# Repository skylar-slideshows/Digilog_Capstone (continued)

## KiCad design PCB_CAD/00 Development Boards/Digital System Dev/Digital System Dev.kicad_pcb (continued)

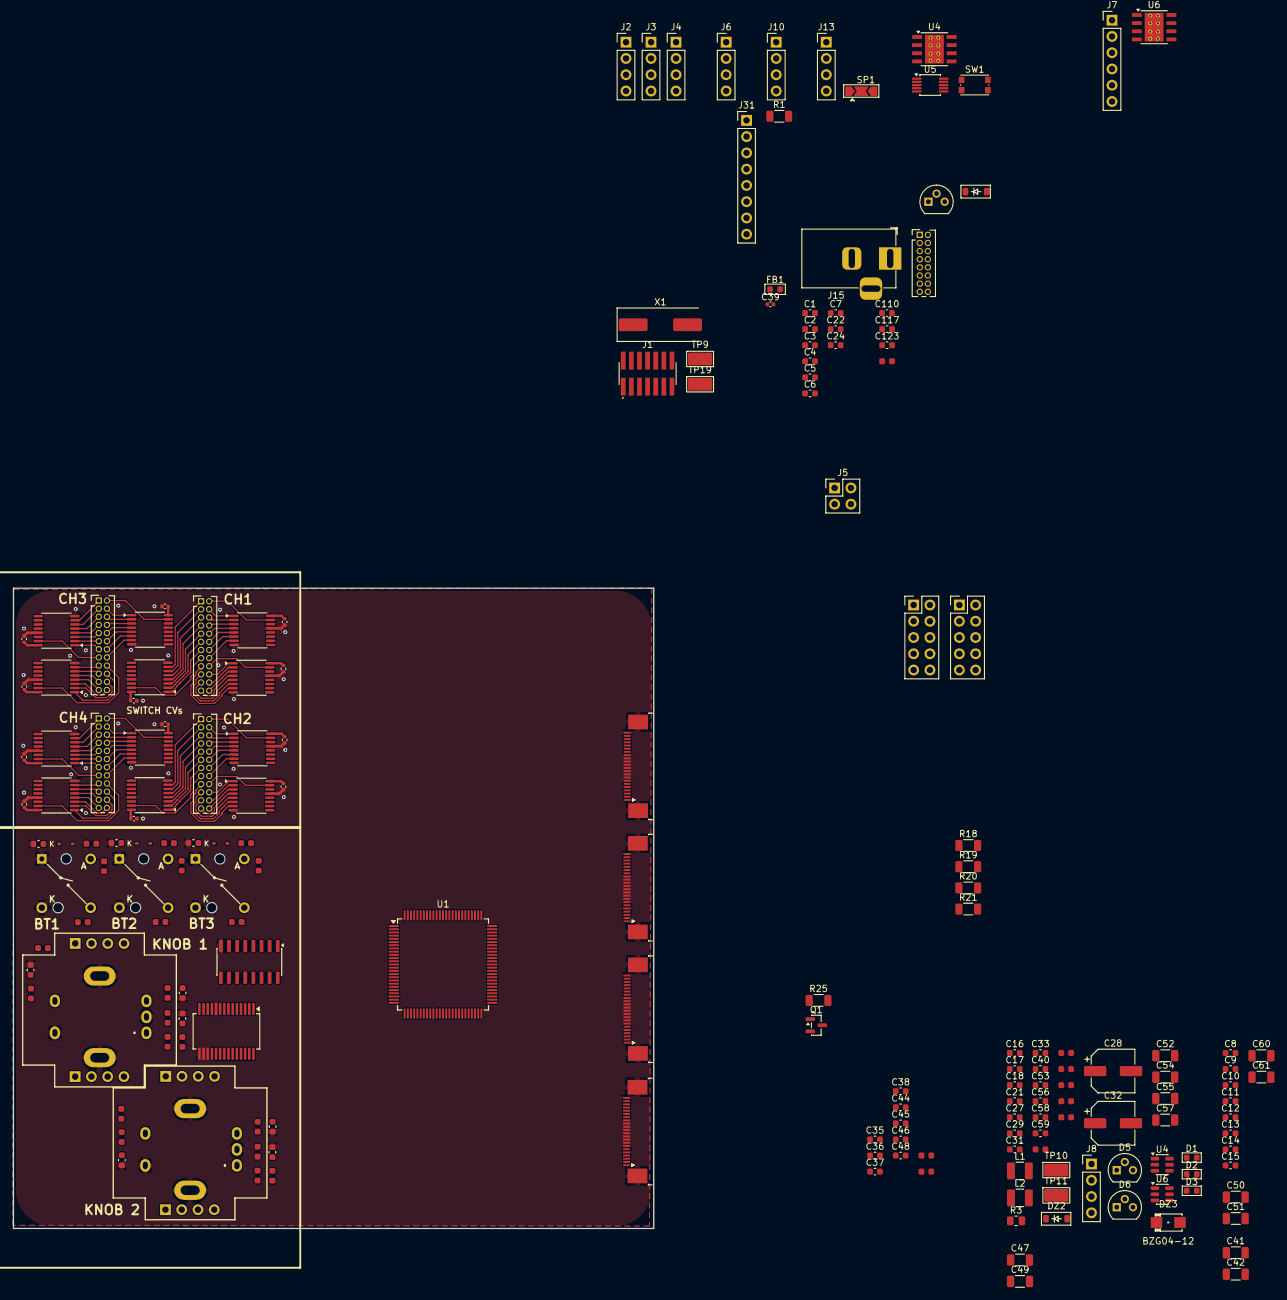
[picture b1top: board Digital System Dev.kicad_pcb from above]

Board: 6 copper layers, 100.0 x 100.0 mm, 189 parts (0 on the bottom side), 209 nets.

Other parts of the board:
C47, C49: 10u; C_1206_3216Metric
U4#2, U6#2: TPS54302DDCT; SOT-23-6

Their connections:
+3V3: C47.1, C49.1; also elsewhere on the board
+10V: U4#2.3 (VIN), U6#2.3 (VIN); also elsewhere on the board
unnamed 215: U4#2.4 (FB); also elsewhere on the board
unnamed 216: U4#2.2 (SW); also elsewhere on the board
unnamed 217: U6#2.4 (FB); also elsewhere on the board
unnamed 218: U6#2.2 (SW); also elsewhere on the board

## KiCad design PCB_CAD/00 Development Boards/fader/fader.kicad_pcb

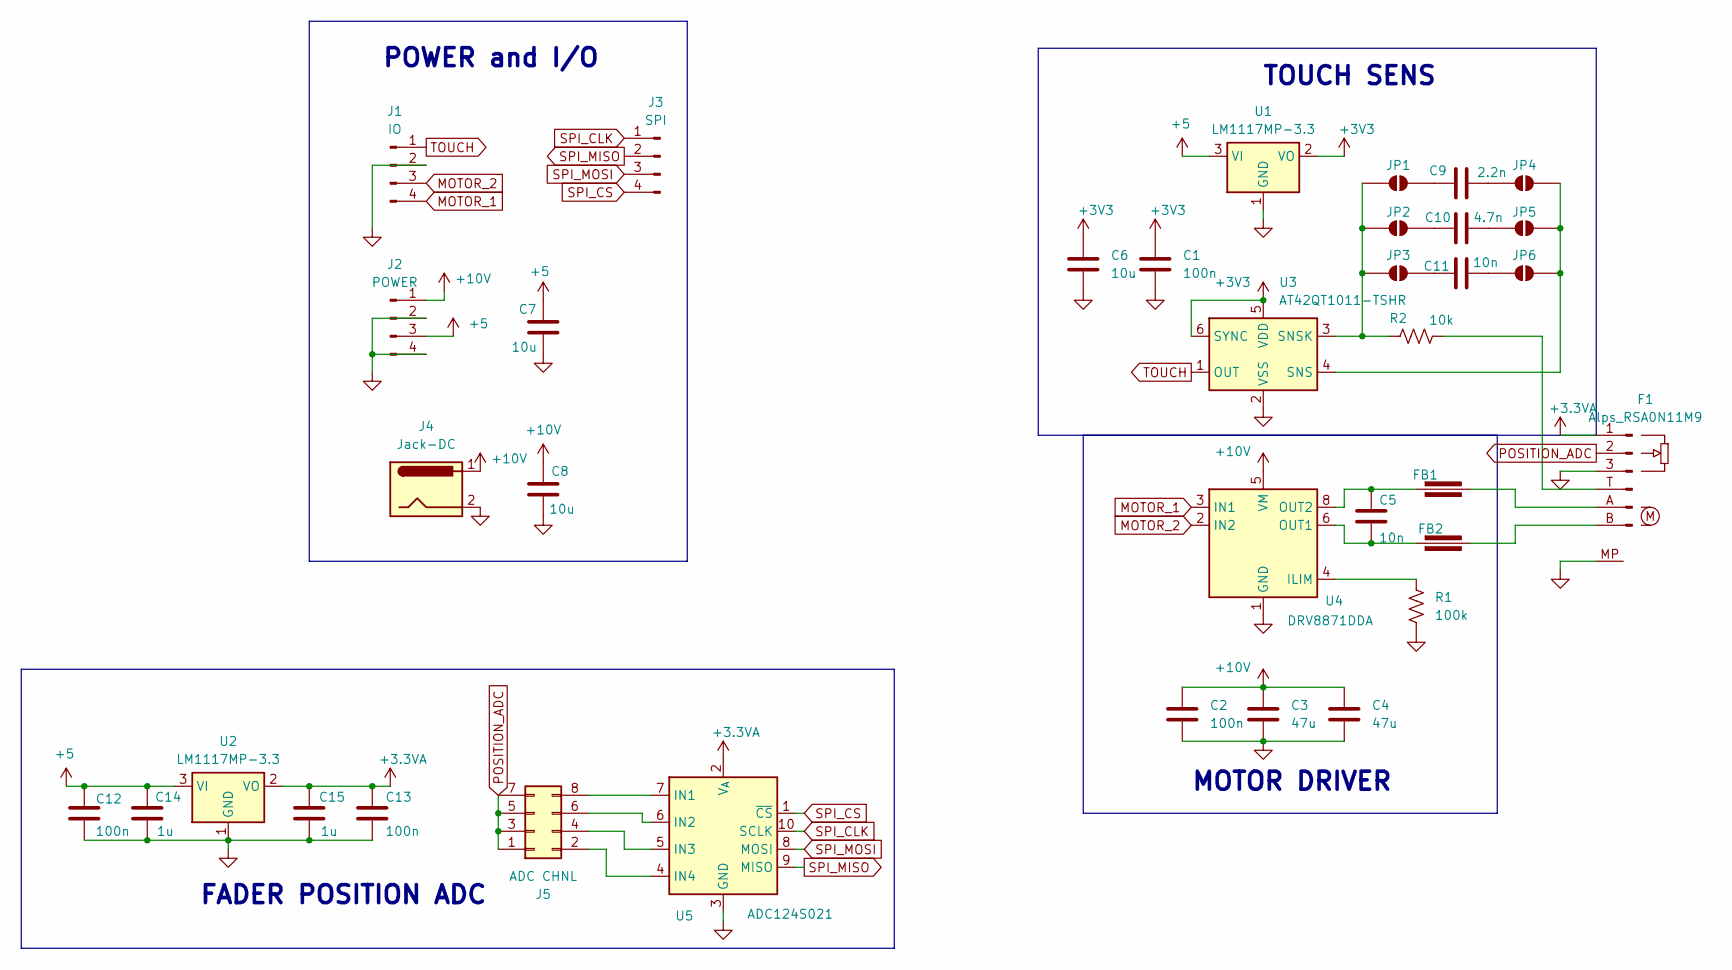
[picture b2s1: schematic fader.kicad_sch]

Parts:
C1, C2, C12: 100n; C_Disc_D10.5mm_W5.0mm_P5.00mm
C3, C4: 47u; CP_Radial_D6.3mm_P2.50mm
C5, C11: 10n; C_Disc_D10.5mm_W5.0mm_P5.00mm
C6, C7, C8: 10u; CP_Radial_D10.0mm_P5.00mm
C9: 2.2n; C_Disc_D10.5mm_W5.0mm_P5.00mm
C10: 4.7n; C_Disc_D10.5mm_W5.0mm_P5.00mm
C13: 100n; CP_EIA-3216-18_Kemet-A; LCSC C7173
C14, C15: 1u; C_Disc_D10.5mm_W5.0mm_P5.00mm
F1: Alps_RSA0N11M9; TRIM_RSA0N11M9A07
FB1, FB2: Ferrite_Bead; LairdTech_28C0236-0JW-10
J1: IO; PinHeader_1x04_P2.54mm_Vertical
J2: POWER; PinHeader_1x04_P2.54mm_Vertical
J3: SPI; PinHeader_1x04_P2.54mm_Vertical
J4: Jack-DC; BarrelJack_Horizontal
J5: ADC CHNL; PinHeader_2x04_P2.54mm_Vertical
JP1, JP2, JP3, JP4, JP5, JP6: SolderJumper_2_Open; SolderJumper-2_P1.3mm_Open_TrianglePad1.0x1.5mm
R1: 100k; R_Axial_DIN0207_L6.3mm_D2.5mm_P10.16mm_Horizontal
R2: 10k; R_Axial_DIN0207_L6.3mm_D2.5mm_P10.16mm_Horizontal
U1, U2: LM1117MP-3.3; SOT-223-3_TabPin2; LCSC C6186
U3: AT42QT1011-TSHR; SOT-23-6; LCSC C112956
U4: DRV8871DDA; Texas_HTSOP-8-1EP_3.9x4.9mm_P1.27mm_EP2.95x4.9mm_Mask2.4x3.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; LCSC C75864
U5: ADC124S021; VSSOP-10_3x3mm_P0.5mm; LCSC C201562

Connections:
+3.3VA: C13.1, C15.1, F1.1, U2.2 (VO), U5.2 (V_{A})
+3V3: C1.1, C6.1, U1.2 (VO), U3.5 (VDD), U3.6 (SYNC)
+5: C7.1, C12.1, C14.1, J2.3, U1.3 (VI), U2.3 (VI)
+10V: C2.1, C3.1, C4.1, C8.1, J2.1, J4.1, U4.5 (VM)
GND: C1.2, C2.2, C3.2, C4.2, C6.2, C7.2, C8.2, C12.2, C13.2, C14.2, C15.2, F1.3, F1.MP, J1.2, J2.2, J2.4, J4.2, R1.2, U1.1 (GND), U2.1 (GND), U3.2 (VSS), U4.1 (GND), U4.7 (GND), U4.9 (GND), U5.3 (GND)
MOTOR_1: J1.4, U4.3 (IN1)
MOTOR_2: J1.3, U4.2 (IN2)
unnamed: F1.T (Pin_4), R2.2
unnamed: F1.A (Pin_5), FB1.2
unnamed: F1.B (Pin_6), FB2.2
unnamed: J5.2, U5.4 (IN4)
unnamed: J5.4, U5.5 (IN3)
unnamed: J5.6, U5.6 (IN2)
unnamed: J5.8, U5.7 (IN1)
unnamed: JP1.1 (A), JP2.1 (A), JP3.1 (A), R2.1, U3.3 (SNSK)
unnamed: C9.1, JP1.2 (B)
unnamed: C10.1, JP2.2 (B)
unnamed: C11.1, JP3.2 (B)
unnamed: C9.2, JP4.1 (A)
unnamed: JP4.2 (B), JP5.2 (B), JP6.2 (B), U3.4 (SNS)
unnamed: C10.2, JP5.1 (A)
unnamed: C11.2, JP6.1 (A)
unnamed: R1.1, U4.4 (ILIM)
unnamed: C5.2, FB2.1, U4.6 (OUT1)
unnamed: C5.1, FB1.1, U4.8 (OUT2)
POSITION_ADC: F1.2, J5.1, J5.3, J5.5, J5.7
SPI_CLK: J3.1, U5.10 (SCLK)
SPI_CS: J3.4, U5.1 (~CS)
SPI_MISO: J3.2, U5.9 (MISO)
SPI_MOSI: J3.3, U5.8 (MOSI)
TOUCH: J1.1, U3.1 (OUT)

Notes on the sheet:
FADER POSITION ADC
TOUCH SENS
MOTOR DRIVER
POWER and I/O

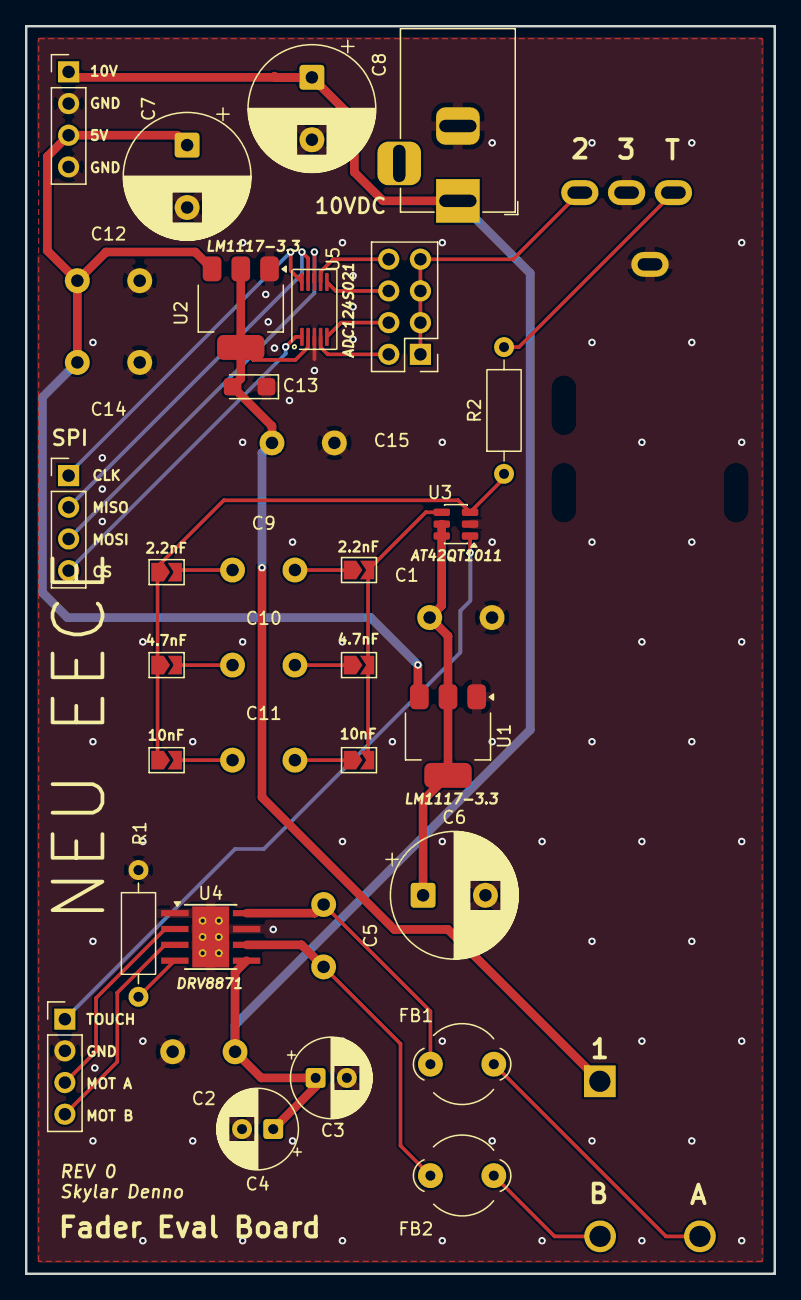
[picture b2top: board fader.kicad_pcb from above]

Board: 4 copper layers, 60.0 x 100.0 mm, 36 parts (0 on the bottom side), 31 nets.

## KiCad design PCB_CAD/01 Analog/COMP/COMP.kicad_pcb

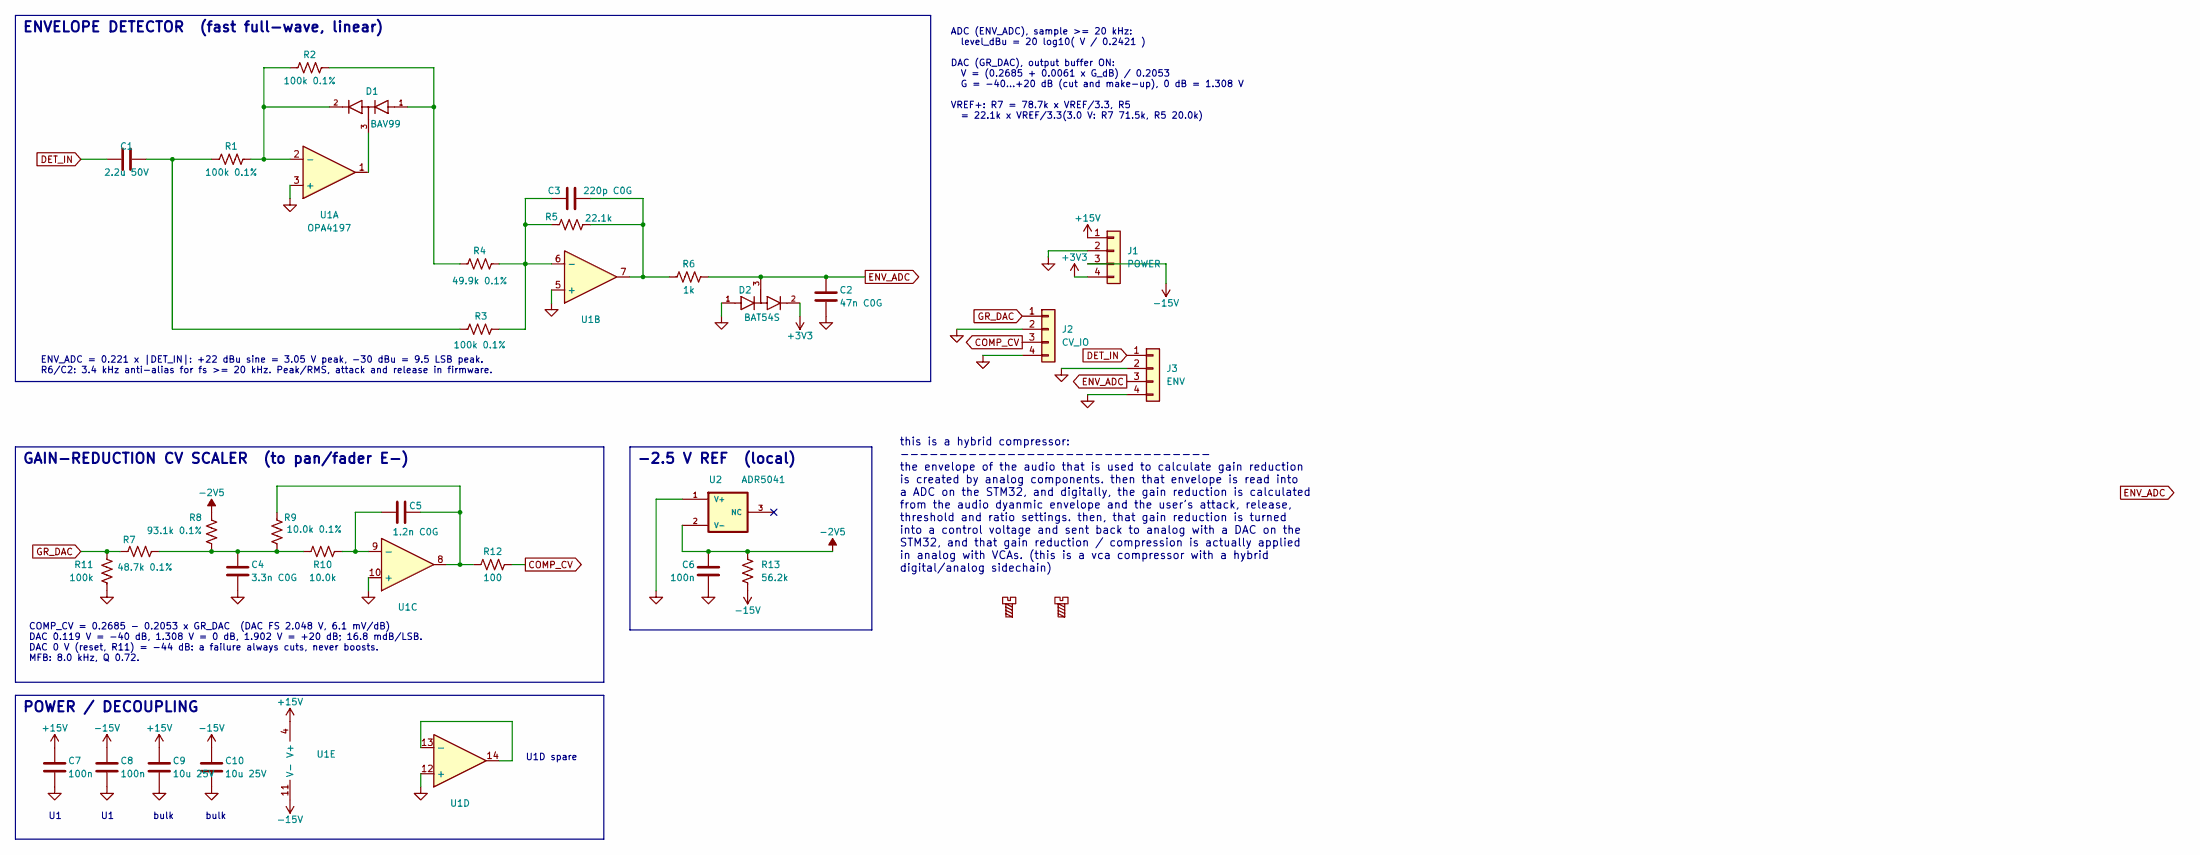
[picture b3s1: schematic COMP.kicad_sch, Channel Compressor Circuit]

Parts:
C1: 2.2u 50V; C_1206_3216Metric; LCSC C50254
C2: 47n C0G; C_Rect_L10.0mm_W2.5mm_P7.50mm_MKS4; LCSC dnp
C3: 220p C0G; C_0603_1608Metric; LCSC C106210
C4: 3.3n C0G; C_0603_1608Metric; LCSC C107048
C5: 1.2n C0G; C_0603_1608Metric; LCSC C527067
C6, C7, C8: 100n; C_0603_1608Metric; LCSC C1590
C9, C10: 10u 25V; C_1206_3216Metric; LCSC C9807
D1: BAV99; SOT-23; LCSC C2500
D2: BAT54S; SOT-23; LCSC C12765
H1, H2: MountingScrew; MountingHole_2.2mm_M2
J1: POWER; PinHeader_1x04_P2.54mm_Vertical; LCSC dnp
J2: CV_IO; PinHeader_1x04_P2.54mm_Vertical; LCSC dnp
J3: ENV; PinHeader_1x04_P2.54mm_Vertical; LCSC dnp
R1, R2, R3: 100k 0.1%; R_0603_1608Metric; LCSC C122538
R4: 49.9k 0.1%; R_0603_1608Metric; LCSC C311894
R5: 22.1k; R_0603_1608Metric; LCSC C137768
R6: 1k; R_0603_1608Metric; LCSC C21190
R7: 48.7k 0.1%; R_0603_1608Metric; LCSC C667111
R8: 93.1k 0.1%; R_0603_1608Metric; LCSC C705799
R9: 10.0k 0.1%; R_0603_1608Metric; LCSC C95204
R10: 10.0k; R_0603_1608Metric; LCSC C95204
R11: 100k; R_0603_1608Metric; LCSC C122538
R12: 100; R_0603_1608Metric; LCSC C122970
R13: 56.2k; R_0603_1608Metric; LCSC C23080
U1: OPA4197; SOIC-14_3.9x8.7mm_P1.27mm; LCSC C2058532
U2: ADR5041; SOT-23; LCSC C659594

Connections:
+3V3: D2.2 (K2), J1.4
+15V: C7.1, C9.1, J1.1, U1.4 (V+)
-2V5: C6.1, R8.1, R13.1, U2.2 (V-)
-15V: C8.1, C10.1, J1.3, R13.2, U1.11 (V-)
COMP_CV: J2.3, R12.2
DET_IN: C1.1, J3.1
ENV_ADC: C2.1, D2.3 (K1A2), J3.3, R6.2
GND: C2.2, C4.2, C6.2, C7.2, C8.2, C9.2, C10.2, D2.1 (A1), J1.2, J2.2, J2.4, J3.2, J3.4, R11.2, U1.3 (+), U1.5 (+), U1.10 (+), U1.12 (+), U2.1 (V+)
GR_DAC: J2.1, R7.1, R11.1
unnamed: C1.2, R1.1, R3.1
unnamed: C3.2, R5.2, R6.1, U1.7
unnamed: C4.1, R7.2, R8.2, R9.2, R10.1
unnamed: C5.2, R9.1, R12.1, U1.8
unnamed: D1.1 (A1), R2.2, R4.1
unnamed: D1.3 (K1A2), U1.1
unnamed: D1.2 (K2), R1.2, R2.1, U1.2 (-)
unnamed: C3.1, R3.2, R4.2, R5.1, U1.6 (-)
unnamed: C5.1, R10.2, U1.9 (-)
unnamed: U1.13 (-), U1.14

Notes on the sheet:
-2.5 V REF (local)
GAIN-REDUCTION CV SCALER (to pan/fader E-)
POWER / DECOUPLING
bulk
this is a hybrid compressor: -------------------------------- the envelope of the audio that is used to calculate gain reduction is created by analog components. then that envelope is read into a ADC on the STM32, and digitally, the gain reduction is calculated from the audio dyanmic envelope and t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
ADC (ENV_ADC), sample >= 20 kHz: level_dBu = 20 log10( V / 0.2421 ) DAC (GR_DAC), output buffer ON: V = (0.2685 + 0.0061 x G_dB) / 0.2053 G = -40...+20 dB (cut and make-up), 0 dB = 1.308 V VREF+: R7 = 78.7k x VREF/3.3, R5 = 22.1k x VREF/3.3(3.0 V: R7 71.5k, R5 20.0k)
COMP_CV = 0.2685 - 0.2053 x GR_DAC (DAC FS 2.048 V, 6.1 mV/dB) DAC 0.119 V = -40 dB, 1.308 V = 0 dB, 1.902 V = +20 dB; 16.8 mdB/LSB. DAC 0 V (reset, R11) = -44 dB: a failure always cuts, never boosts. MFB: 8.0 kHz, Q 0.72.
ENV_ADC = 0.221 x |DET_IN|: +22 dBu sine = 3.05 V peak, -30 dBu = 9.5 LSB peak. R6/C2: 3.4 kHz anti-alias for fs >= 20 kHz. Peak/RMS, attack and release in firmware.
ENVELOPE DETECTOR (fast full-wave, linear)
U1D spare

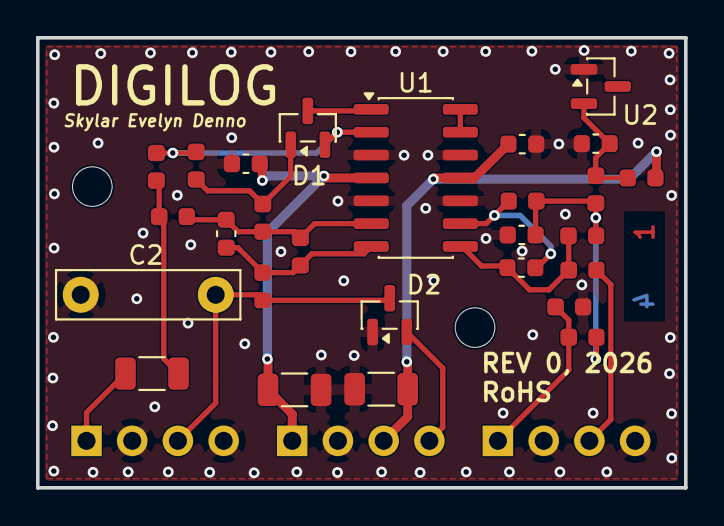
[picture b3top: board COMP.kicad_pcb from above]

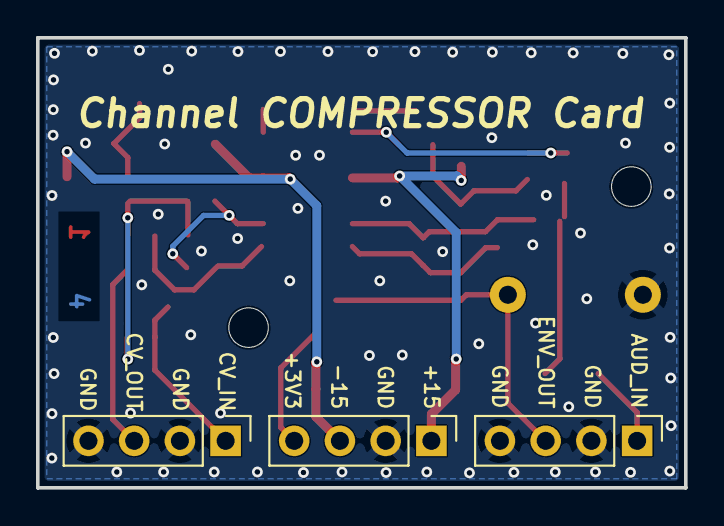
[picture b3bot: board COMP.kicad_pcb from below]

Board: 4 copper layers, 36.0 x 25.0 mm, 32 parts (3 on the bottom side), 19 nets.

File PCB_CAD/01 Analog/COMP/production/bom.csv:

Designator,Footprint,Quantity,Value,LCSC Part #
C1,1206,1,2.2u 50V,C50254
"C10, C9",1206,2,10u 25V,C9807
C2,C_Rect_L10.0mm_W2.5mm_P7.50mm_MKS4,1,47n C0G,dnp
C3,0603,1,220p C0G,C106210
C4,0603,1,3.3n C0G,C107048
C5,0603,1,1.2n C0G,C527067
"C6, C7, C8",0603,3,100n,C1590
D1,SOT-23,1,BAV99,C2500
D2,SOT-23,1,BAT54S,C12765
J1,PinHeader_1x04_P2.54mm_Vertical,1,POWER,dnp
J2,PinHeader_1x04_P2.54mm_Vertical,1,CV_IO,dnp
J3,PinHeader_1x04_P2.54mm_Vertical,1,ENV,dnp
"R1, R2, R3",0603,3,100k 0.1%,C122538
R10,0603,1,10.0k,C95204
R11,0603,1,100k,C122538
R12,0603,1,100,C122970
R13,0603,1,56.2k,C23080
R4,0603,1,49.9k 0.1%,C311894
R5,0603,1,22.1k,C137768
R6,0603,1,1k,C21190
R7,0603,1,48.7k 0.1%,C667111
R8,0603,1,93.1k 0.1%,C705799
R9,0603,1,10.0k 0.1%,C95204
U1,SOIC-14_3.9x8.7mm_P1.27mm,1,OPA4197,C2058532
U2,SOT-23,1,ADR5041,C659594

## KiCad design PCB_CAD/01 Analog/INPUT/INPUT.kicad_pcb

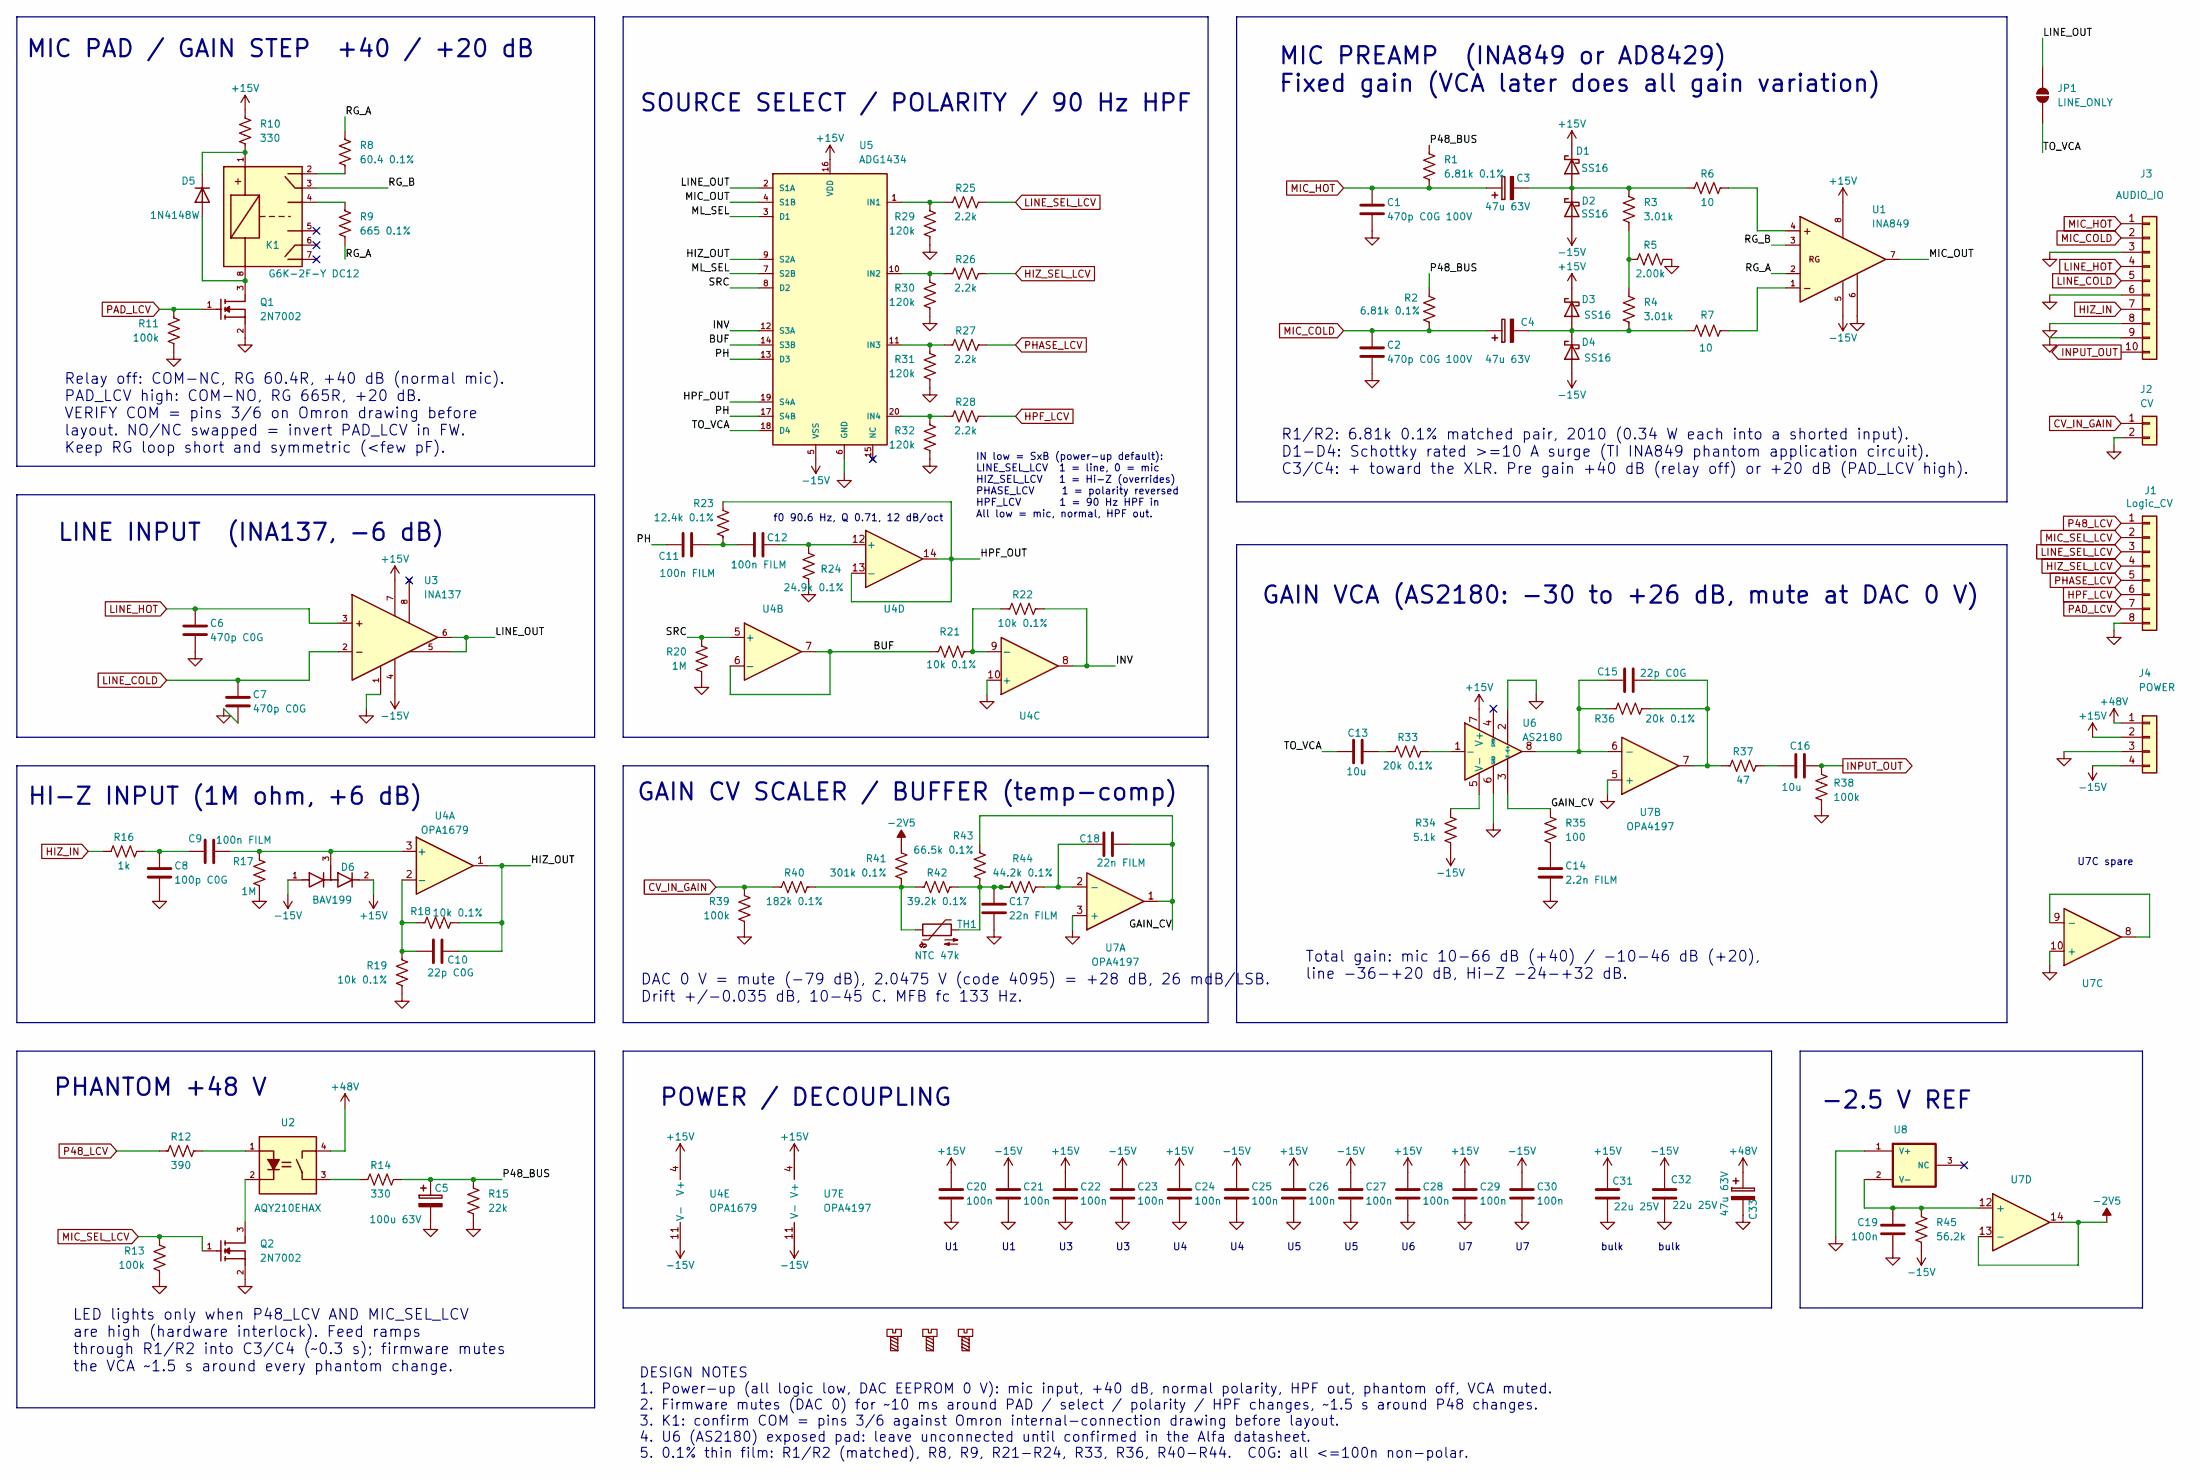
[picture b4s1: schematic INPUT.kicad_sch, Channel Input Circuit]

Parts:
C1, C2: 470p C0G 100V; C_0603_1608Metric; LCSC C326973
C3, C4, C33: 47u 63V; CP_Elec_6.3x7.7; LCSC C48971005
C5: 100u 63V; CP_Elec_10x10.5; LCSC C51953411
C6, C7: 470p C0G; C_0603_1608Metric; LCSC C326973
C8: 100p C0G; C_0603_1608Metric; LCSC C14665
C9, C11, C12: 100n FILM; C_1812_4532Metric; LCSC C569829
C10, C15: 22p C0G; C_0603_1608Metric; LCSC C105620
C13, C16: 10u; CP_Elec_6.3x5.4_Nichicon; LCSC C340735
C14: 2.2n FILM; C_0603_1608Metric; LCSC C178417
C17, C18: 22n FILM; C_Rect_L7.2mm_W2.5mm_P5.00mm; LCSC _DNP_
C19, C20, C21, C22, C23, C24, C25, C26, C27, C28, C29, C30: 100n; C_0603_1608Metric; LCSC C1590
C31, C32: 22u 25V; C_1210_3225Metric; LCSC C21397
D1, D2, D3, D4: SS16; D_SMA; LCSC C2481
D5: 1N4148W; D_SOD-123; LCSC C2099
D6: BAV199; SOT-23; LCSC C145516
H1, H2, H3: MountingScrew; MountingHole_2.2mm_M2; LCSC _DNP_
J1: Logic_CV; PinHeader_1x08_P2.54mm_Vertical; LCSC _DNP_
J2: CV; PinHeader_1x02_P2.54mm_Vertical; Part Number 1-0201FBV0T; LCSC _DNP_
J3: AUDIO_IO; PinHeader_1x10_P2.54mm_Vertical; LCSC _DNP_
J4: POWER; PinHeader_1x04_P2.54mm_Vertical; LCSC _DNP_
JP1: LINE_ONLY; SolderJumper-2_P1.3mm_Open_TrianglePad1.0x1.5mm; LCSC _DNP_
K1: G6K-2F-Y DC12; Relay_DPDT_Omron_G6K-2F-Y; LCSC C397194
Q1, Q2: 2N7002; SOT-23; LCSC C8545
R1, R2: 6.81k 0.1%; R_2010_5025Metric; LCSC C54102447
R3, R4: 3.01k; R_0603_1608Metric; LCSC C137732
R5: 2.00k; R_0603_1608Metric; LCSC C318130
R6, R7: 10; R_0603_1608Metric; LCSC C217691
R8: 60.4 0.1%; R_0402_1005Metric; LCSC C852867
R9: 665 0.1%; R_0603_1608Metric; LCSC C861514
R10, R14: 330; R_1206_3216Metric; LCSC C17930
R11, R13, R38, R39: 100k; R_0603_1608Metric; LCSC C122538
R12: 390; R_0603_1608Metric; LCSC C351650
R15: 22k; R_1206_3216Metric; LCSC C25654
R16: 1k; R_0603_1608Metric; LCSC C110776
R17, R20: 1M; R_0603_1608Metric; LCSC C234360
R18, R19, R21, R22: 10k 0.1%; R_0603_1608Metric; LCSC C95204
R23: 12.4k 0.1%; R_0603_1608Metric; LCSC C861102
R24: 24.9k 0.1%; R_0603_1608Metric; LCSC C667077
R25, R26, R27, R28: 2.2k; R_0603_1608Metric; LCSC C309092
R29, R30, R31, R32: 120k; R_0603_1608Metric; LCSC C136959
R33, R36: 20k 0.1%; R_0603_1608Metric; LCSC C190611
R34: 5.1k; R_0603_1608Metric; LCSC C122969
R35: 100; R_0603_1608Metric; LCSC C122970
R37: 47; R_0603_1608Metric; LCSC C218045
R40: 182k 0.1%; R_0603_1608Metric; LCSC C861170
R41: 301k 0.1%; R_0603_1608Metric; LCSC C861309
R42: 39.2k 0.1%; R_0603_1608Metric; LCSC C861369
R43: 66.5k 0.1%; R_0402_1005Metric; LCSC C851084
R44: 44.2k 0.1%; R_0402_1005Metric; LCSC C705633
R45: 56.2k; R_0402_1005Metric; LCSC C36157922
TH1: NTC 47k; R_Axial_DIN0207_L6.3mm_D2.5mm_P2.54mm_Vertical; LCSC _DNP_
U1: INA849; MSOP-8_3x3mm_P0.65mm; LCSC C4370731
U2: AQY210EHAX; SMDIP-4_W9.53mm; LCSC C24728
U3: INA137; SOIC-8_3.9x4.9mm_P1.27mm; LCSC C2652878
U4: OPA1679; TSSOP-14_4.4x5mm_P0.65mm; LCSC C2057264
U5: ADG1434; TSSOP-20_4.4x6.5mm_P0.65mm; LCSC C408906
U6: AS2180; PinHeader_1x08_P2.54mm_Vertical; LCSC _DNP_
U7: OPA4197; SOIC-14_3.9x8.7mm_P1.27mm; LCSC C2058532
U8: ADR5041; SOT-23; LCSC C2686108

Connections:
+15V: C20.1, C22.1, C24.1, C26.1, C28.1, C29.1, C31.1, D1.1 (K), D3.1 (K), D6.2 (K2), J4.2, R10.1, U1.8 (+VS), U3.7 (V+), U4.4 (V+), U5.16 (VDD), U6.7 (V+), U7.4 (V+)
+48V: C33.1 (+), J4.1, U2.4 (O)
-2V5: R41.1, U7.13 (-), U7.14
-15V: C21.1, C23.1, C25.1, C27.1, C30.1, C32.1, D2.2 (A), D4.2 (A), D6.1 (A1), J4.4, R34.2, R45.2, U1.5 (-VS), U3.4 (V-), U4.11 (V-), U5.5 (VSS), U7.11 (V-)
/BUF: R21.1, U4.6 (-), U4.7, U5.14 (S3B)
/GAIN_CV: C18.2, R35.1, R43.1, U6.3 (E-), U7.1
/HIZ_OUT: C10.2, R18.2, U4.1, U5.9 (S2A)
/HPF_OUT: R23.1, U4.13 (-), U4.14, U5.19 (S4A)
/INV: R22.2, U4.8, U5.12 (S3A)
/LINE_OUT: JP1.2 (B), U3.5 (Sense), U3.6 (Out), U5.2 (S1A)
/MIC_OUT: U1.7 (OUT), U5.4 (S1B)
/ML_SEL: U5.3 (D1), U5.7 (S2B)
/P48_BUS: C5.1 (+), R1.1, R2.1, R14.2, R15.1
/PH: C11.1, U5.13 (D3), U5.17 (S4B)
/RG_A: R8.1, R9.2, U1.2 (RG)
/RG_B: K1.3 (COM1), U1.3 (RG)
/SRC: R20.1, U4.5 (+), U5.8 (D2)
/TO_VCA: C13.1, JP1.1 (A), U5.18 (D4)
CV_IN_GAIN: J2.1, R39.1, R40.1
GND: C1.2, C2.2, C5.2 (-), C6.2, C7.2, C8.2, C14.2, C17.2, C19.2, C20.2, C21.2, C22.2, C23.2, C24.2, C25.2, C26.2, C27.2, C28.2, C29.2, C30.2, C31.2, C32.2, C33.2 (-), J1.8, J2.2, J3.3, J3.6, J3.8, J3.9, J4.3, Q1.2 (S), Q2.2 (S), R5.2, R11.2, R13.2, R15.2, R17.2, R19.2, R20.2, R24.2, R29.2, R30.2, R31.2, R32.2, R38.2, R39.2, U1.6 (REF), U3.1 (Ref), U4.10 (+), U5.6 (GND), U6.2 (E+), U6.6 (GND), U7.3 (+), U7.5 (+), U7.10 (+), U8.1 (V+)
HIZ_IN: J3.7, R16.1
HIZ_SEL_LCV: J1.4, R26.2
HPF_LCV: J1.6, R28.2
INPUT_OUT: C16.2, J3.10, R38.1
LINE_COLD: C7.1, J3.5, U3.2 (-In)
LINE_HOT: C6.1, J3.4, U3.3 (+In)
LINE_SEL_LCV: J1.3, R25.2
MIC_COLD: C2.1, C4.1 (+), J3.2, R2.2
MIC_HOT: C1.1, C3.1 (+), J3.1, R1.2
MIC_SEL_LCV: J1.2, Q2.1 (G), R13.1
unnamed: C3.2 (-), D1.2 (A), D2.1 (K), R3.1, R6.1
unnamed: C4.2 (-), D3.2 (A), D4.1 (K), R4.2, R7.1
unnamed: C8.1, C9.1, R16.2
unnamed: C11.2, C12.1, R23.2
unnamed: C13.2, R33.1
unnamed: C14.1, R35.2
unnamed: C15.2, R36.2, R37.1, U7.7
unnamed: C16.1, R37.2
unnamed: C17.1, R42.2, R43.2, R44.1, TH1.2
unnamed: D5.2 (A), K1.8 (-), Q1.3 (D)
unnamed: D5.1 (K), K1.1 (+), R10.2
unnamed: C9.2, D6.3 (K1A2), R17.1, U4.3 (+)
unnamed: K1.2 (NC1), R8.2
unnamed: K1.4 (NO1), R9.1
unnamed: Q2.3 (D), U2.2 (K)
unnamed: R3.2, R4.1, R5.1
unnamed: R14.1, U2.3 (O)
unnamed: R40.2, R41.2, R42.1, TH1.1
unnamed: R6.2, U1.4 (+IN)
unnamed: R7.2, U1.1 (-IN)
unnamed: R12.2, U2.1 (A)
unnamed: C10.1, R18.1, R19.1, U4.2 (-)
unnamed: R21.2, R22.1, U4.9 (-)
unnamed: C12.2, R24.1, U4.12 (+)
unnamed: R25.1, R29.1, U5.1 (IN1)
unnamed: R26.1, R30.1, U5.10 (IN2)
unnamed: R27.1, R31.1, U5.11 (IN3)
unnamed: R28.1, R32.1, U5.20 (IN4)
unnamed: R33.2, U6.1 (-)
unnamed: R34.1, U6.5 (V-)
unnamed: C18.1, R44.2, U7.2 (-)
unnamed: C15.1, R36.1, U6.8, U7.6 (-)
unnamed: U7.8, U7.9 (-)
unnamed: C19.1, R45.1, U7.12 (+), U8.2 (V-)
P48_LCV: J1.1, R12.1
PAD_LCV: J1.7, Q1.1 (G), R11.1
PHASE_LCV: J1.5, R27.2

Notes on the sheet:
DESIGN NOTES 1. Power-up (all logic low, DAC EEPROM 0 V): mic input, +40 dB, normal polarity, HPF out, phantom off, VCA muted. 2. Firmware mutes (DAC 0) for ~10 ms around PAD / select / polarity / HPF changes, ~1.5 s around P48 changes. 3. K1: confirm COM = pins 3/6 against Omron internal-connectio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
MIC PREAMP (INA849 or AD8429) Fixed gain (VCA later does all gain variation)
IN low = SxB (power-up default): LINE_SEL_LCV 1 = line, 0 = mic HIZ_SEL_LCV 1 = Hi-Z (overrides) PHASE_LCV 1 = polarity reversed HPF_LCV 1 = 90 Hz HPF in All low = mic, normal, HPF out.
PHANTOM +48 V
LED lights only when P48_LCV AND MIC_SEL_LCV are high (hardware interlock). Feed ramps through R1/R2 into C3/C4 (~0.3 s); firmware mutes the VCA ~1.5 s around every phantom change.
DAC 0 V = mute (-79 dB), 2.0475 V (code 4095) = +28 dB, 26 mdB/LSB. Drift +/-0.035 dB, 10-45 C. MFB fc 133 Hz.
bulk
U7C spare
POWER / DECOUPLING
GAIN CV SCALER / BUFFER (temp-comp)
Total gain: mic 10-66 dB (+40) / -10-46 dB (+20), line -36-+20 dB, Hi-Z -24-+32 dB.
HI-Z INPUT (1M ohm, +6 dB)
Relay off: COM-NC, RG 60.4R, +40 dB (normal mic). PAD_LCV high: COM-NO, RG 665R, +20 dB. VERIFY COM = pins 3/6 on Omron drawing before layout. NO/NC swapped = invert PAD_LCV in FW. Keep RG loop short and symmetric (<few pF).
f0 90.6 Hz, Q 0.71, 12 dB/oct
LINE INPUT (INA137, -6 dB)
SOURCE SELECT / POLARITY / 90 Hz HPF
GAIN VCA (AS2180: -30 to +26 dB, mute at DAC 0 V)
-2.5 V REF
MIC PAD / GAIN STEP +40 / +20 dB
R1/R2: 6.81k 0.1% matched pair, 2010 (0.34 W each into a shorted input). D1-D4: Schottky rated >=10 A surge (TI INA849 phantom application circuit). C3/C4: + toward the XLR. Pre gain +40 dB (relay off) or +20 dB (PAD_LCV high).

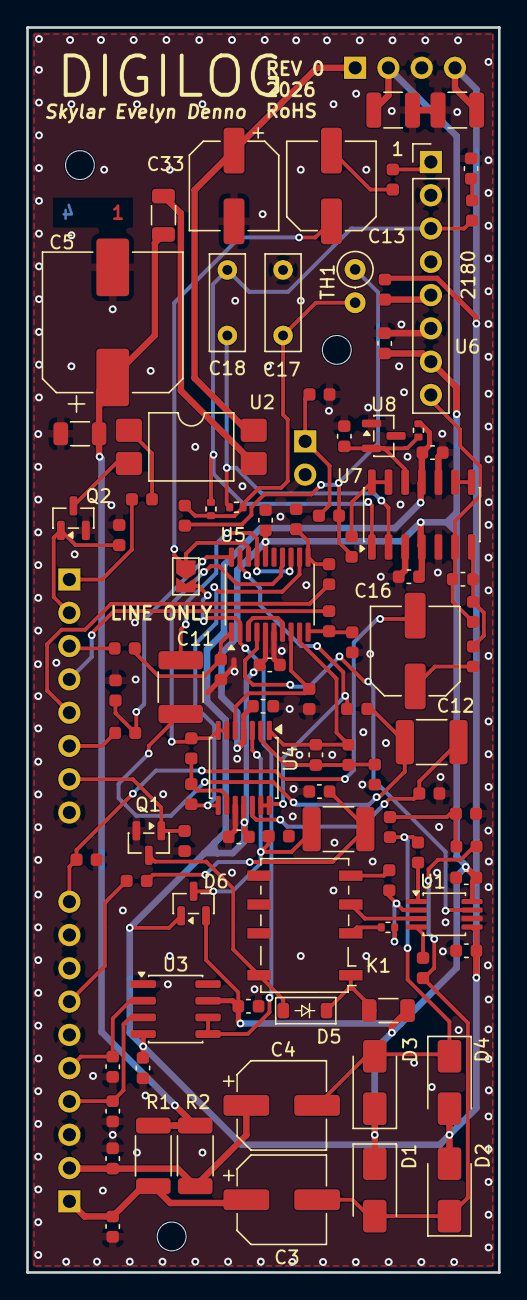
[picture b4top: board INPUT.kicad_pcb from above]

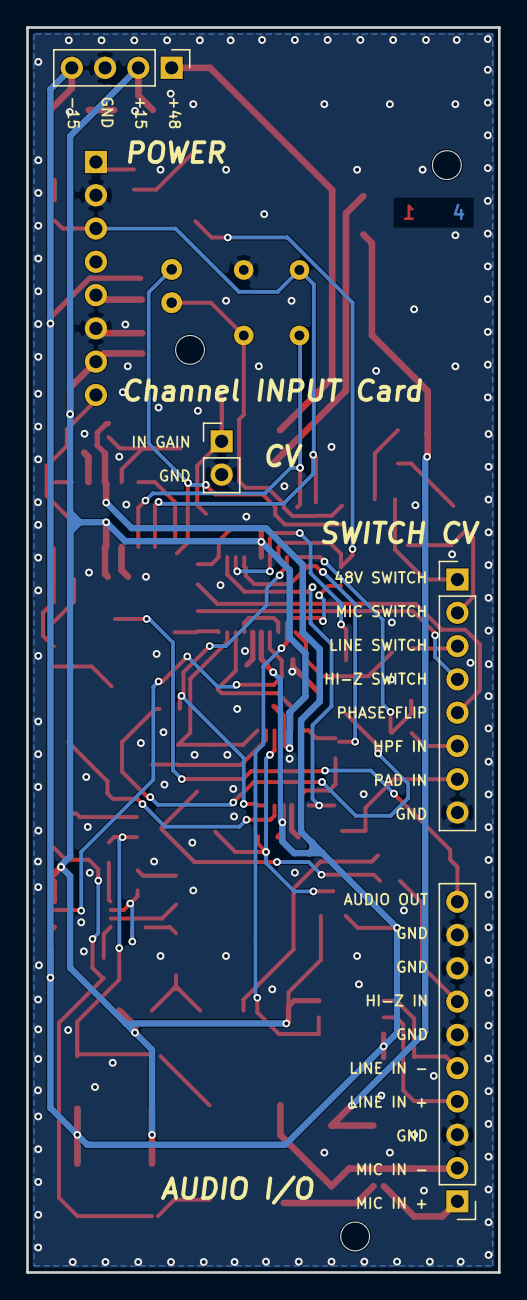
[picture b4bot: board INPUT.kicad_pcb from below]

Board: 4 copper layers, 36.0 x 95.0 mm, 104 parts (4 on the bottom side), 67 nets.

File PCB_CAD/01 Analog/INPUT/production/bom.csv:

Designator,Footprint,Quantity,Value,LCSC Part #
"C1, C2",0603,2,470p C0G 100V,C326973
"C10, C15",0603,2,22p C0G,C105620
"C11, C12, C9",1812,3,100n FILM,C569829
"C13, C16",CP_Elec_6.3x5.4_Nichicon,2,10u,C340735
C14,0603,1,2.2n FILM,C178417
"C17, C18",C_Rect_L7.2mm_W2.5mm_P5.00mm,2,22n FILM,_DNP_
"C19, C20, C21, C22, C23, C24, C25, C26, C27, C28, C29, C30",0603,12,100n,C1590
"C3, C33, C4",CP_Elec_6.3x7.7,3,47u 63V,C48971005
"C31, C32",1210,2,22u 25V,C21397
C5,CP_Elec_10x10.5,1,100u 63V,C51953411
"C6, C7",0603,2,470p C0G,C326973
C8,0603,1,100p C0G,C14665
"D1, D2, D3, D4",D_SMA,4,SS16,C2481
D5,D_SOD-123,1,1N4148W,C2099
D6,SOT-23,1,BAV199,C145516
J1,PinHeader_1x08_P2.54mm_Vertical,1,Logic_CV,_DNP_
J2,PinHeader_1x02_P2.54mm_Vertical,1,CV,_DNP_
J3,PinHeader_1x10_P2.54mm_Vertical,1,AUDIO_IO,_DNP_
J4,PinHeader_1x04_P2.54mm_Vertical,1,POWER,_DNP_
K1,Relay_DPDT_Omron_G6K-2F-Y,1,G6K-2F-Y DC12,C397194
"Q1, Q2",SOT-23,2,2N7002,C8545
"R1, R2",2010,2,6.81k 0.1%,C54102447
"R10, R14",1206,2,330,C17930
"R11, R13, R38, R39",0603,4,100k,C122538
R12,0603,1,390,C351650
R15,1206,1,22k,C25654
R16,0603,1,1k,C110776
"R17, R20",0603,2,1M,C234360
"R18, R19, R21, R22",0603,4,10k 0.1%,C95204
R23,0603,1,12.4k 0.1%,C861102
R24,0603,1,24.9k 0.1%,C667077
"R25, R26, R27, R28",0603,4,2.2k,C309092
"R29, R30, R31, R32",0603,4,120k,C136959
"R3, R4",0603,2,3.01k,C137732
"R33, R36",0603,2,20k 0.1%,C190611
R34,0603,1,5.1k,C122969
R35,0603,1,100,C122970
R37,0603,1,47,C218045
R40,0603,1,182k 0.1%,C861170
R41,0603,1,301k 0.1%,C861309
R42,0603,1,39.2k 0.1%,C861369
R43,0402,1,66.5k 0.1%,C851084
R44,0402,1,44.2k 0.1%,C705633
R45,0402,1,56.2k,C36157922
R5,0603,1,2.00k,C318130
"R6, R7",0603,2,10,C217691
R8,0402,1,60.4 0.1%,C852867
R9,0603,1,665 0.1%,C861514
TH1,R_Axial_DIN0207_L6.3mm_D2.5mm_P2.54mm_Vertical,1,NTC 47k,_DNP_
U1,MSOP-8_3x3mm_P0.65mm,1,INA849,C4370731
U2,SMDIP-4_W9.53mm,1,AQY210EHAX,C24728
U3,SOIC-8_3.9x4.9mm_P1.27mm,1,INA137,C2652878
U4,TSSOP-14_4.4x5mm_P0.65mm,1,OPA1679,C2057264
U5,TSSOP-20_4.4x6.5mm_P0.65mm,1,ADG1434,C408906
U6,PinHeader_1x08_P2.54mm_Vertical,1,AS2180,_DNP_
U7,SOIC-14_3.9x8.7mm_P1.27mm,1,OPA4197,C2058532
U8,SOT-23,1,ADR5041,C2686108
